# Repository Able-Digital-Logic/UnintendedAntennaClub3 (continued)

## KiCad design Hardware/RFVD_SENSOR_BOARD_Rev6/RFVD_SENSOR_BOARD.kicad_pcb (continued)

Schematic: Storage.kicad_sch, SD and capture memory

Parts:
C601: 100nF 50V X7R; C_0402_1005Metric; MPN CL05B104KB54PNC; LCSC C307331
C602: 47uF 10V POLY; CP_EIA-3528-21_Kemet-B; MPN T520B476M010ATE035; LCSC C141441
C603: 100nF 50V X7R; C_0402_1005Metric; MPN CL05B104KB54PNC; JLCPCB_PN C307331
C604: 1uF 25V X7R; C_0603_1608Metric; MPN CL10B105KA8NNNC; JLCPCB_PN C29936
J601: DM3AT-SF-PEJM5; microSD_HC_Hirose_DM3AT-SF-PEJM5; MPN DM3AT-SF-PEJM5; JLCPCB_PN C114218
R601: 1R 5% 1/16W; R_0402_1005Metric; MPN FRC0402J1R0 TS; JLCPCB_PN C2906901
R602, R603: 33R 1% 1/10W; R_0603_1608Metric; MPN 0603WAF330JT5E; JLCPCB_PN C23140
R604: 4.7k 1% 1/10W; R_0603_1608Metric; MPN 0603WAF4701T5E; JLCPCB_PN C23162
RN601: 47R x4; R_Array_Convex_4x0402; MPN 4D02WGJ0470TCE; JLCPCB_PN C55183
U601: EMIF06-MSD02N16; ST_EMIF06-MSD02N16_uQFN-16_3.5x1.2mm_P0.4mm; MPN EMIF06-MSD02N16; JLCPCB_PN C5267594
U602: APS6404L-3SQR-SN; SOIC-8_3.9x4.9mm_P1.27mm; MPN APS6404L-3SQR-SN; JLCPCB_PN C5333729

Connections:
+3V3_D: C603.1, C604.1, R601.1, R604.1, U602.8 (VDD); also elsewhere on the board
/SD and capture memory/+3V3_SD: C601.1, C602.1, J601.4 (VDD), R601.2, U601.16 (VCC), U601.17 (RDATA_VCC)
/SD and capture memory/PSRAM_CLK_MCU: R603.1; also elsewhere on the board
/SD and capture memory/PSRAM_CS_N: R604.2, U602.1 (~CE); also elsewhere on the board
/SD and capture memory/PSRAM_IO0_MCU: RN601.1 (R1.1); also elsewhere on the board
/SD and capture memory/PSRAM_IO0_RAM: RN601.8 (R1.2), U602.5 (SI/SIO0)
/SD and capture memory/PSRAM_IO1_MCU: RN601.3 (R3.1); also elsewhere on the board
/SD and capture memory/PSRAM_IO1_RAM: RN601.6 (R3.2), U602.2 (SO/SIO1)
/SD and capture memory/PSRAM_IO2_MCU: R602.1; also elsewhere on the board
/SD and capture memory/PSRAM_IO2_RAM: R602.2, U602.3 (SIO2)
/SD and capture memory/PSRAM_IO3_MCU: RN601.2 (R2.1); also elsewhere on the board
/SD and capture memory/PSRAM_IO3_RAM: RN601.7 (R2.2), U602.7 (SIO3)
/SD and capture memory/SD_CD_N: J601.9 (DET_B), U601.1 (WP/CD); also elsewhere on the board
/SD and capture memory/SD_CLK: J601.5 (CLK), U601.12 (CLK_Ex)
/SD and capture memory/SD_CLK_MCU: U601.6 (CLK_In); also elsewhere on the board
/SD and capture memory/SD_CMD: J601.3 (CMD), U601.13 (CMD_Ex)
/SD and capture memory/SD_CMD_MCU: U601.5 (CMD_In); also elsewhere on the board
/SD and capture memory/SD_D0: J601.7 (DAT0), U601.11 (DAT0_Ex)
/SD and capture memory/SD_D0_MCU: U601.7 (DAT0_In); also elsewhere on the board
/SD and capture memory/SD_D1: J601.8 (DAT1), U601.10 (DAT1_Ex)
/SD and capture memory/SD_D1_MCU: U601.8 (DAT1_In); also elsewhere on the board
/SD and capture memory/SD_D2: J601.1 (DAT2), U601.15 (DAT2_Ex)
/SD and capture memory/SD_D2_MCU: U601.3 (DAT2_In); also elsewhere on the board
/SD and capture memory/SD_D3: J601.2 (DAT3/CD), U601.14 (DAT3_Ex)
/SD and capture memory/SD_D3_MCU: U601.4 (DAT3_In); also elsewhere on the board
GND: C601.2, C602.2, C603.2, C604.2, J601.6 (VSS), J601.10 (DET_A), J601.SH (SHIELD), U601.19 (GND), U602.4 (VSS); also elsewhere on the board
unnamed: R603.2, U602.6 (SCLK)

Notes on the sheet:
OUT
I/O
MCU via U601 to J601
SD-side CMD/DAT/CLK
Preallocate recording files and qualify the card's write latency. Stop recording before removing the card. An ordinary SD card does not guarantee file integrity after sudden power loss.
PWR
Socket-side signal nodes
Clock and memory select
PSRAM_CLK_MCU / CS_N
Quad read/write data
Bypass / common return
Card clock
LOCAL
SD_CLK_MCU, SD_CMD_MCU, SD_D0..D3_MCU, SD_CD_N
U602 provides 8 MiB; firmware reserves 6 MiB for queued data. Keep each CE-low interval within 8 us for the selected temperature grade. Check timing with SD traffic and display updates active.
NE-20: R601 isolates card write-current steps from +3V3_D. +3V3_SD feeds J601.4, C601, C602 and U601 VCC/RDATA_VCC (EMIF06 90k pull-ups, ESD).
PSRAM_IO0..3_MCU
Purpose
Command and four-bit data
Place protection near J601 with short returns to the common ground plane. Component ESD ratings do not establish immunity of the assembled port.
MCU to U602
J601 / U601 WP-CD to MCU
SHEET INTERFACE: bus ports. Each member joins its label on this sheet by name.
Card-detect state
SD_CLK_MCU
PSRAM data damping
Source / destination
Signal / bus
SD card and capture queue
S-17: RN601 (47R x4) is the only damping on IO0/IO1/IO3, at U401 pins 58-60; R602 33R at U401 pin 1. No RAM-side resistor (APS6404L drives at 50R). Qualify read and write timing at the loaded pins.
PSRAM_CLK_MCU, PSRAM_CS_N, PSRAM_IO0..IO3_MCU
Power to U602 and J601
SD_CD_N
SD_CMD / DAT0..3
MCU via RN601 / R602 to U602
S-19(a): U601 EMIF06-MSD02N16 = 45R + pi filter (<= 20 pF) per line, 90k pull-ups, 8 kV contact ESD. DAT3 pull-up: RDATA_VCC tied to VCC (ST Fig. 2/9). RDAT3_GND (470k pull-down) unused. Firmware: SDMMC1 GPIO speed medium (no MCU-side source resistor).
+3V3_D / GND
U601 to J601 (filtered, ESD)

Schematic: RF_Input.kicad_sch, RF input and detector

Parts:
C701: 100nF 50V X7R; C_0603_1608Metric; MPN CC0603KRX7R9BB104; LCSC C14663
C702: 1uF 25V X7R; C_0603_1608Metric; MPN CL10B105KA8NNNC; LCSC C29936
C703, C704: 100pF 50V C0G; C_0402_1005Metric; MPN GRM1555C1H101JA01D; LCSC C77177
C705, C706: 1nF 50V C0G; C_0402_1005Metric; MPN GRM1555C1H102JA01D; LCSC C76947
C707: 1nF 50V C0G; C_0402_1005Metric; MPN GRM1555C1H102JA01D; JLCPCB_PN C76947
C708: 47pF 100V C0G 1%; C_0603_1608Metric; MPN GCM1885C2A470FA16D; JLCPCB_PN C882574
C709: 100nF 50V X7R; C_0402_1005Metric; MPN CL05B104KB54PNC; JLCPCB_PN C307331
C710: 100nF 50V X7R; C_0402_1005Metric; MPN CL05B104KB54PNC; LCSC C307331
D701, D702: PESD5V0H1BSF; PESD2V5Y1BSF_SOD962-2_ManufacturerLand; MPN PESD5V0H1BSFYL; JLCPCB_PN C478002
FL701: NFM18PC104R1C3D; Murata_NFM18PC_0603_3T; MPN NFM18PC104R1C3D; JLCPCB_PN C111493
J701: CAL_IN; U.FL_Hirose_U.FL-R-SMT-1_Vertical; MPN U.FL-R-SMT-1(80); JLCPCB_PN C88374
J702: AIMD_IN; U.FL_Hirose_U.FL-R-SMT-1_Vertical; MPN U.FL-R-SMT-1(80); LCSC C88374
R701: 3.32k 0.1% 1/16W; R_0402_1005Metric; MPN RT0402BRD073K32L; JLCPCB_PN C852762
R702, R706: 1.50k 0.1% 1/16W; R_0402_1005Metric; MPN RT0402BRD071K5L; JLCPCB_PN C281775
R703, R704: 100R 0.1% 1/10W; R_0603_1608Metric; MPN RT0603BRD07100RL; JLCPCB_PN C122970
R705: DNP; R_0603_1608Metric; not fitted
TP701: VRMS_DIAG; TestPoint_Pad_D1.0mm; MPN DNP-NO-COMPONENT; LCSC N/A
U701: TLV809EA46DBZR; SOT-23-3; MPN TLV809EA46DBZR; LCSC C1852111
U702: ADL5511ACPZ-R7; LFCSP-16-1EP_3x3mm_P0.5mm_EP1.6x1.6mm; MPN ADL5511ACPZ-R7; JLCPCB_PN C579159

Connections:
+5V_A: FL701.1; also elsewhere on the board
/Analog acquisition/EREF_RAW: U702.9 (EREF); also elsewhere on the board
/Analog acquisition/VENV_RAW: U702.10 (VENV); also elsewhere on the board
/RF input and detector/+5V_RF: C701.1, C702.1, C704.1, C705.2, C706.2, C709.1, C710.2, FL701.3, U701.3 (VDD), U702.15 (VPOS)
/RF input and detector/CAL_IN: C707.1, D702.1 (A1), J701.1 (In), R703.1, R704.1
/RF input and detector/CAL_INJ: C707.2, R701.1
/RF input and detector/RFIN: C708.2, D701.1 (A1), R701.2, U702.2 (RFIN)
/RF input and detector/VRMS_DIAG: TP701.1 (1_1), U702.11 (VRMS)
GND: C701.2, C702.2, C703.2, C704.2, C709.2, D701.2 (A2), D702.2 (A2), FL701.2, J701.2 (Ext), J702.2 (Ext), R703.2, R704.2, R705.2, U701.1 (GND), U702.5 (COMM), U702.17 (EP); also elsewhere on the board
unnamed: C708.1, R702.2
unnamed: J702.1 (In), R705.1, R706.2
unnamed: R702.1, R706.1
unnamed: U701.2 (RESET_n), U702.4 (ENBL)
unnamed: C703.1, U702.3 (FLT1)
unnamed: C705.1, U702.16 (FLT2)
unnamed: C706.1, U702.1 (FLT3)
unnamed: C710.1, U702.14 (FLT4)

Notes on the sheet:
LOCAL
OUT
AIMD coax -> R706/R702/C708
FLT2-4 caps return to +5V_RF
+5V_A (FL701 -> +5V_RF) / GND
U701 / C703,C705,C710,C706 -> U702
R701 sets permanent loading (-6..-7.5 % of k) and coupling (H_inj ~ -24 dB). Default 3.32k; 4.99k/10k trade coupling for loading. D702 + D701 = two-stage ESD path (D701 required). Keep R706/R702/R701 in the same Yageo RT thin-film series.
Sense the loaded terminal RF voltage.
Analog supply and coax return.
Power-up enable and detector filtering.
Source / destination
AC coupling and RF input protection.
C708/D701 -> detector
RF input and envelope detector
ENBL / FLT1..4
RF envelope, offset by EREF.
CAL_IN port J701: relative self-test and cross-unit calibration injection into the detector node (RFIN). +20 dBm CW max (termination-limited); never exceed. Remove the W1 jumper and the shield before any RECORD. Never plug the AIMD coax into CAL. R703||R704 = 50 ohm load.
Module interfaces
VRMS_DIAG / TP701
Purpose
PWR
Detector offset-reference voltage.
Power -> detector
U702 pin 9 -> Analog
U702 pin 11 -> probe
U702 pin 10 -> Analog
AIMD_IN at J702
Input limit at J702 (model; confirm in X10): <= 22 Vpk CW at 127.74 MHz, <= 24 Vpk CW at 63.86 MHz, no 40 Vpk CW soak. ADL5511 RFIN 5.6 Vpp abs max binds at about 28.5-29.3 Vpk (de-embedded S1P), so larger R706/R702 alone do not raise it; keep pulses below 28 Vpk until X10 measures it.
VENV_RAW
Connect the characterized AIMD coax at J702. R706/R702 attenuate; they do not form a 50 ohm match. Calibrate the complete cable and input at 64 and 128 MHz. Avoid RF probe stubs.
I/O
RFIN at U702 pin 2
RMS diagnostic; not a recorded ADC input.
Signal / bus
EREF_RAW

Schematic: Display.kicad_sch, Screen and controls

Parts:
C801, C802: 47pF 50V C0G; C_0402_1005Metric; MPN 0402CG470J500NT; JLCPCB_PN C1567
C803, C805, C809: 1uF 25V X7R; C_0603_1608Metric; MPN CL10B105KA8NNNC; JLCPCB_PN C29936
C804, C806, C807, C808, C811: 100nF 50V X7R; C_0402_1005Metric; MPN CL05B104KB54PNC; JLCPCB_PN C307331
C810: 100pF 50V C0G; C_0402_1005Metric; MPN GRM1555C1H101JA01D; JLCPCB_PN C77177
D801, D802, D803, D804: NSI45020A; D_SOD-123; MPN NSI45020AT1G; JLCPCB_PN C128367
F801: 200mA PTC; Fuse_0603_1608Metric; MPN BSMD0603-020-16V; JLCPCB_PN C883092
FB801: 600R@100MHz; L_0603_1608Metric; MPN BLM18AG601SN1D; JLCPCB_PN C19330
J801: XF2M-4015-1A; Omron_XF2M-4015-1A_1x40-1MP_P0.5mm_Horizontal; MPN XF2M-4015-1A; JLCPCB_PN C225713
J802: 84953-6; TE_84953-6_1x06-1MP_P1.0mm_Horizontal; MPN 84953-6; JLCPCB_PN C408826
Q801: 2N7002; SOT-23; MPN 2N7002; JLCPCB_PN C8545
Q802: AO3401A; SOT-23; MPN AO3401A; JLCPCB_PN C15127
Q803: AO3400A; SOT-23; MPN AO3400A; JLCPCB_PN C20917
R801, R813, R814: 4.7k 1% 1/10W; R_0603_1608Metric; MPN 0603WAF4701T5E; JLCPCB_PN C23162
R802, R803, R806, R812: 100k 0.1% 1/10W; R_0603_1608Metric; MPN RT0603BRD07100KL; JLCPCB_PN C122538
R804, R811: 100R 1% 1/16W; R_0402_1005Metric; MPN 0402WGF1000TCE; JLCPCB_PN C25076
R805, R809, R815: 10k 1% 1/16W; R_0402_1005Metric; MPN 0402WGF1002TCE; JLCPCB_PN C25744
R807, R808: 1k 1% 1/16W; R_0402_1005Metric; MPN 0402WGF1001TCE; JLCPCB_PN C11702
R810: 100k 1% 1/16W; R_0402_1005Metric; MPN 0402WGF1003TCE; JLCPCB_PN C25741
RN801, RN802, RN803: 47R x4; R_Array_Convex_4x0402; MPN 4D02WGJ0470TCE; JLCPCB_PN C55183
SW801: RECORD / STOP; SW_SPST_B3U-1000P; MPN B3U-1000P; JLCPCB_PN C231329
SW802: MARK; SW_SPST_B3U-1000P; MPN B3U-1000P; JLCPCB_PN C231329
TP801, TP802, TP803: DISP_GND; TestPoint_Pad_3.0x3.0mm; MPN PCB pad (no part)
U801: TPS2553DDBVR; SOT-23-6; MPN TPS2553DDBVR; JLCPCB_PN C521201

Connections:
+3V3_D: C805.1, R801.1, U801.1 (IN); also elsewhere on the board
+3V3_UI: C803.2, C804.2, C806.1, C811.1, J801.7, J801.8, J801.13, J801.31, J802.1, R805.1, R813.1, R814.1, R815.1, U801.6 (OUT)
/STM32H743 controller/LCD_BL: R811.1; also elsewhere on the board
/STM32H743 controller/LCD_CS_N_MCU: RN803.3 (R3.1); also elsewhere on the board
/STM32H743 controller/LCD_D0_MCU: RN801.1 (R1.1); also elsewhere on the board
/STM32H743 controller/LCD_D1_MCU: RN801.2 (R2.1); also elsewhere on the board
/STM32H743 controller/LCD_D2_MCU: RN803.4 (R4.1); also elsewhere on the board
/STM32H743 controller/LCD_D3_MCU: RN803.2 (R2.1); also elsewhere on the board
/STM32H743 controller/LCD_D4_MCU: RN802.1 (R1.1); also elsewhere on the board
/STM32H743 controller/LCD_D5_MCU: RN802.2 (R2.1); also elsewhere on the board
/STM32H743 controller/LCD_D6_MCU: RN802.3 (R3.1); also elsewhere on the board
/STM32H743 controller/LCD_D7_MCU: RN802.4 (R4.1); also elsewhere on the board
/STM32H743 controller/LCD_DC_MCU: R804.1; also elsewhere on the board
/STM32H743 controller/LCD_RST: J801.30, R806.1; also elsewhere on the board
/STM32H743 controller/LCD_WR_N_MCU: RN803.1 (R1.1); also elsewhere on the board
/STM32H743 controller/MARK_N_MCU: C808.1, R808.1; also elsewhere on the board
/STM32H743 controller/RECORD_N_MCU: C807.1, R807.1; also elsewhere on the board
/STM32H743 controller/TP_INT: J802.5, R815.2; also elsewhere on the board
/STM32H743 controller/TP_RST: J802.6; also elsewhere on the board
/STM32H743 controller/TP_SCL: J802.3, R813.2; also elsewhere on the board
/STM32H743 controller/TP_SDA: J802.4, R814.2; also elsewhere on the board
/STM32H743 controller/UI_EN: Q801.1 (G), R802.1, U801.3 (EN); also elsewhere on the board
/STM32H743 controller/UI_FAULT_N: R801.2, U801.4 (~FAULT); also elsewhere on the board
/Screen and controls/LCD_BL_SW: D801.1 (K), D802.1 (K), D803.1 (K), D804.1 (K), Q803.3 (D)
/Screen and controls/LCD_CS_N: C801.1, J801.10, RN803.6 (R3.2)
/Screen and controls/LCD_D0: J801.22, RN801.8 (R1.2)
/Screen and controls/LCD_D1: J801.23, RN801.7 (R2.2)
/Screen and controls/LCD_D2: J801.24, RN803.5 (R4.2)
/Screen and controls/LCD_D3: J801.25, RN803.7 (R2.2)
/Screen and controls/LCD_D4: J801.26, RN802.8 (R1.2)
/Screen and controls/LCD_D5: J801.27, RN802.7 (R2.2)
/Screen and controls/LCD_D6: J801.28, RN802.6 (R3.2)
/Screen and controls/LCD_D7: J801.29, RN802.5 (R4.2)
/Screen and controls/LCD_DC: J801.11, R804.2
/Screen and controls/LCD_LED_A: C809.1, C810.1, FB801.2, J801.38
/Screen and controls/LCD_LED_K1: D801.2 (A), J801.34
/Screen and controls/LCD_LED_K2: D802.2 (A), J801.35
/Screen and controls/LCD_LED_K3: D803.2 (A), J801.36
/Screen and controls/LCD_LED_K4: D804.2 (A), J801.37
/Screen and controls/LCD_WR_N: C802.1, J801.12, RN803.8 (R1.2)
/Screen and controls/MARK_N: R808.2, SW802.1
/Screen and controls/RECORD_N: R807.2, SW801.1
GND: C801.2, C802.2, C803.1, C804.1, C805.2, C806.2, C807.2, C808.2, C809.2, C810.2, C811.2, J801.1, J801.9, J801.14, J801.15, J801.16, J801.17, J801.18, J801.19, J801.20, J801.21, J801.32, J801.33, J801.39, J801.MP (MountPin), J802.2, J802.MP (MountPin), Q801.2 (S), Q803.2 (S), R802.2, R803.2, R805.2, R806.2, R812.2, SW801.2, SW802.2, TP801.1 (1_1), TP802.1 (1_1), TP803.1 (1_1), U801.2 (GND); also elsewhere on the board
unnamed: Q801.3 (D), R809.2
unnamed: FB801.1, Q802.3 (D)
unnamed: Q802.1 (G), R809.1, R810.2
unnamed: F801.2, Q802.2 (S), R810.1
unnamed: Q803.1 (G), R811.2, R812.1
unnamed: R803.1, U801.5 (ILIM)
VSYS: F801.1; also elsewhere on the board

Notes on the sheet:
IN / OUT
OUT
Signal / bus
Power enable / overcurrent flag
MCU and touch module
Supply and ground; no ground split
U801 to J801
Display, touch and physical controls
+3V3_UI / local bypass
U801 switches the 3.3 V screen supply (+3V3_UI) and reports overcurrent. Current-limit range: 234 to 303 mA (R803 100k 0.1%, S-25); panel + touch ~40 mA max. No bulk cap on +3V3_UI (C68 removed, S-12): no 190 mA inrush on +3V3_D at UI_EN; firmware UI power-cycle guard >= 50 ms. Backlight (LED-A) is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
MCU and U801
Display data and control
Active-low recording controls
I/O
PWR
MCU to J801
Power sheet / common return
Source / destination
J801: Newhaven NHD-2.4-240320AF-CSXP-CTP (ST7789Vi, 8080-II 8-bit on DB8-DB15, write-only) via Omron XF2M-4015-1A; also fits NHD-2.8-...-FCTP. IM2:IM0 = 001 hard-tied (NHD Interface Selection p.5); RDX (J801.13) tied to +3V3_UI, PD4 (FMC_NOE) unused: firmware never reads the panel (S-11). J802: FT5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
RECORD_N / MARK_N
UI_EN / UI_FAULT_N
TP_RST / TP_INT
Reset / touch-ready indication
SHEET INTERFACE: bus ports. Each member joins its label on this sheet by name.
Touch I2C; +3V3_UI pull-ups
LCD FMC D0-D7/WR/RD/CS/DC, RST, BL
Switched screen rail; sequence I/O
UI_EN, UI_FAULT_N, RECORD_N_MCU, MARK_N_MCU
LOCAL
SW801 / SW802 via 1k R807 / R808 to MCU
Purpose
TP_SCL, TP_SDA, TP_INT, TP_RST
LCD_D0..D7_MCU, LCD_WR_N_MCU, LCD_DC_MCU, LCD_CS_N_MCU, LCD_RST, LCD_BL
SW801 starts/stops recording; SW802 marks an event. Both remain usable without the touchscreen.
+3V3_D / GND
TP_SCL / TP_SDA
Start with UI power off; set safe GPIO states before switching power. Acquisition and SD service take priority over rendering. Calibration needs a known external stimulus.

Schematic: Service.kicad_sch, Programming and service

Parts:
J901: TC2030-NL SWD POGO DNP; Tag-Connect_TC2030-IDC-NL_2x03_P1.27mm_Vertical; MPN DNP-NO-COMPONENT; LCSC N/A
TP901: GND_SERVICE; TestPoint_Pad_D1.0mm; MPN PCB_PAD

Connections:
+3V3_D: J901.1 (VCC); also elsewhere on the board
/Programming and service/NRST: J901.3 (~RESET); also elsewhere on the board
/Programming and service/SWCLK: J901.4 (SWCLK); also elsewhere on the board
/Programming and service/SWDIO: J901.2 (SWDIO); also elsewhere on the board
GND: J901.5 (GND), TP901.1 (1_1); also elsewhere on the board

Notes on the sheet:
Programming; trace via RTT/USB CDC.
J901 probe <-> MCU
External and MCU reset path.
Spare; console on USB CDC.
R401 pad 1 at U401 pin 94
Purpose
PWR
RECORD+MARK chord / USB
LOCAL
Board -> probe voltage sense
NRST
Programming and service
+3V3_D / GND
SWD POGO / SERVICE ONLY
3.3V logic reference; avoid backpower.
Disconnect during exposure
DFU entry
PA9 / PA10 (ex-UART1)
I/O
Module interfaces
SWCLK / SWDIO (SWO NC)
OUT / I/O
Source / destination
J901 <-> MCU
Signal / bus
BOOT0
Bench recovery: strap to +3V3_D.
none (J7 removed)
Boot stub jumps to ROM DFU.

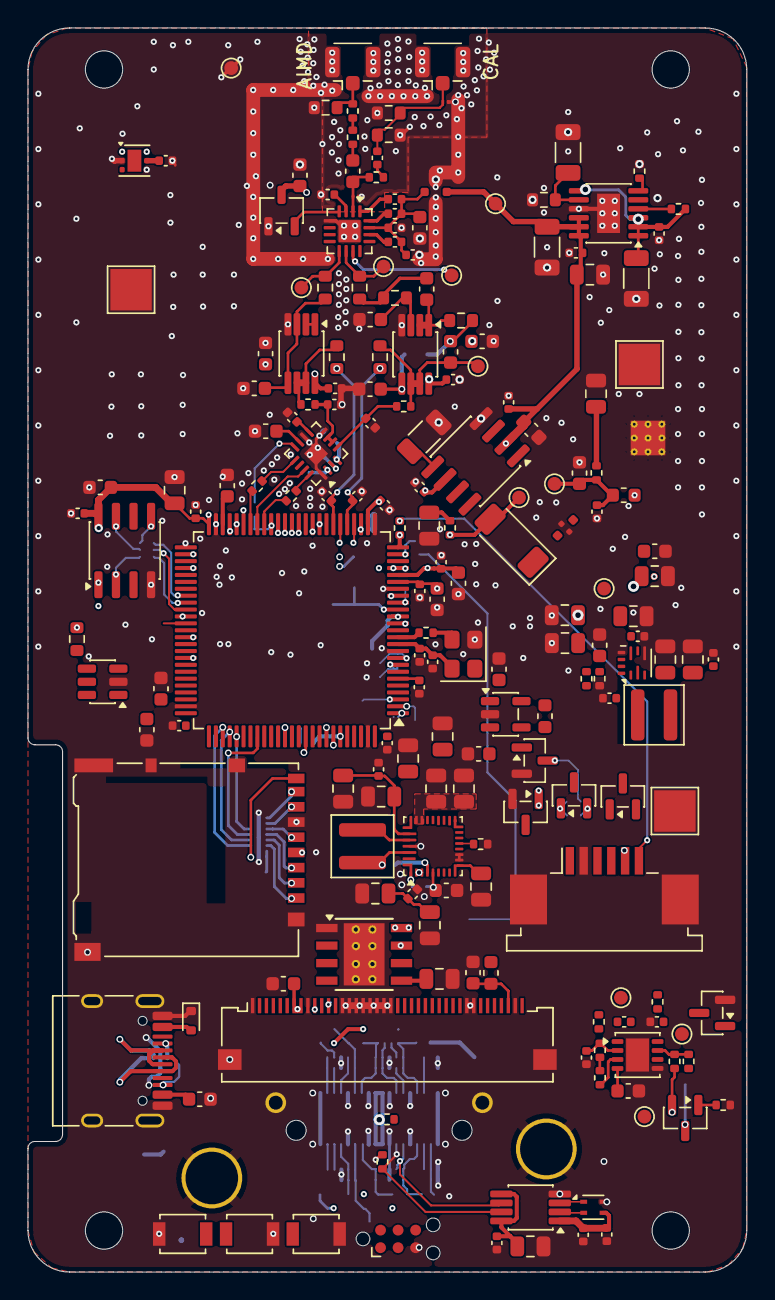
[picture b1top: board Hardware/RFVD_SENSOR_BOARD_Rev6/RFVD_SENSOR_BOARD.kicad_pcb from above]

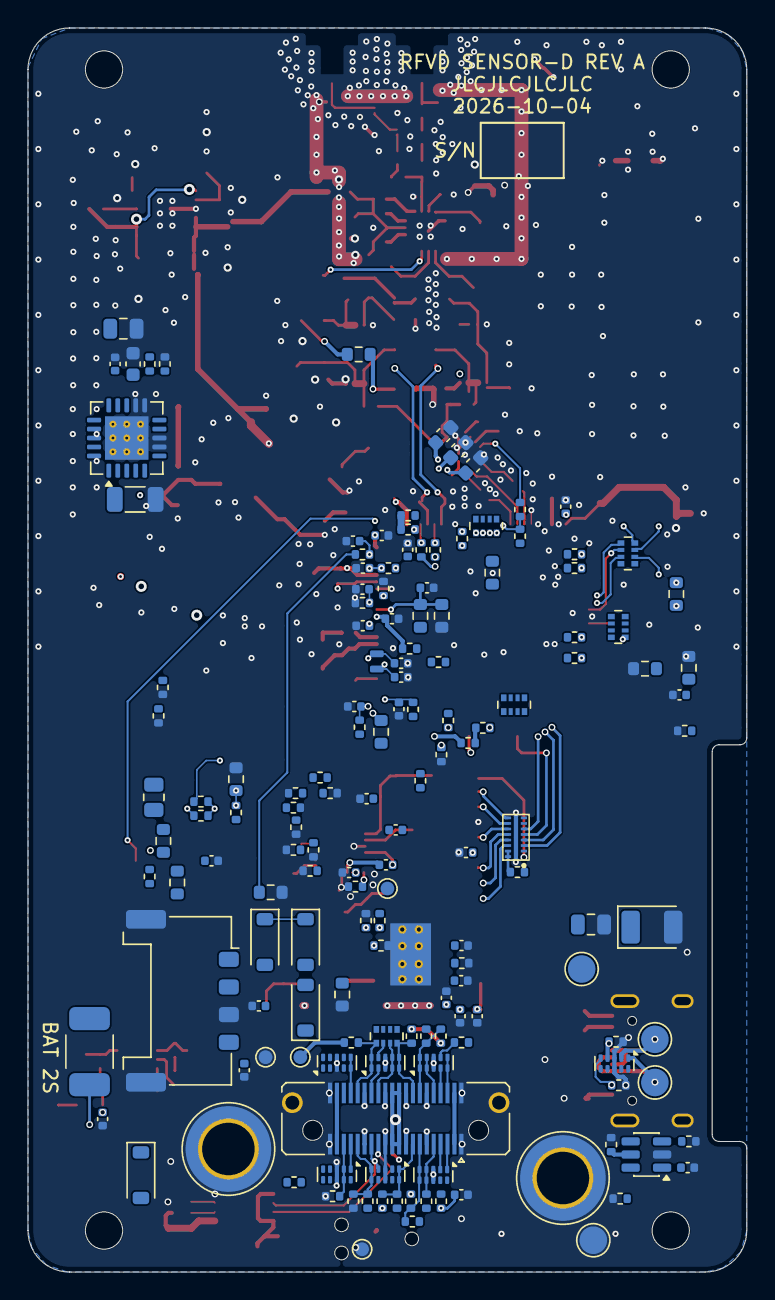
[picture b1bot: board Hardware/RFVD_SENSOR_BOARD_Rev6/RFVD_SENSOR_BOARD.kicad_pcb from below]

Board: 6 copper layers, 52.0 x 90.0 mm, 348 parts (153 on the bottom side), 230 nets.

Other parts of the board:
H1, H2, H3, H4: MountingHole_2.7mm
